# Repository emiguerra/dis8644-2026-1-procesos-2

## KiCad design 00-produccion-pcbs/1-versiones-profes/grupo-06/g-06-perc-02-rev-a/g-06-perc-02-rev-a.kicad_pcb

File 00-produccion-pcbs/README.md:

# produccion-pcbs

jornada maratónica sábado 06 junio 2026

equipo docente toma todos los proyectos de kicad entregados el día anterior, de proyecto-02, y con eso edita, revisa, y envía a producción.

hay 6 grupos de trabajo con una temática en particular, cada grupo realizó 2 esquemáticos con sus respectivas placas, en varias versiones que subieron a la carpeta 00-proyecto-02.

a continuación los apuntes de las distintas revisiones hechas de estos proyectos, para prepararlos para su producción física.

en este repo creamos 3 carpetas:

- 0-versiones-estudiantes: archivos de kicad con las versiones más recientes de proyectos de estudiantes
- 1-versiones-profes: archivos de kicad con las versiones revisadas y realizadas por equipo docentes
- 2-archivos-produccion: gerbers de producción, etiquetados como revA.

## grupo-01: piezos

- benjaminalvarez21
- Anaysval
- chknngttts
- ryukivol
- nicolasvaldesgreve

### g-01-pie-01-rev-a

- cambiamos tamaño r15
- cambiamos conector de entrada
- cambiamos nomenclatura de "100 u" a "100u"
- cambiamos huella de transistor Q1, porque era la equivocada

### g-01-pie-02-rev-a

- no fue enviado a producción porque no tenemos garantía de que funcionara según lo visto en protoboard.

## grupo-02: secuenciadores

- isidoraalvarez
- tomascatri
- dayanapanitrur
- Estrabismx
- angel-udp

### g-02-sec-01-rev-a

en esquemático:

- agregamos resistor de clock in a ground, para pulldown.
- agregamos resistor entre 4040 Q0 patita 9 y salida
- agregamos resistor a cada salida de jack switch.
- cambiamos huellas de transistores a versión inline_wide para que tengan más espacio
- agregados mounting hole faltantes

en pcb:

- actualizamos conectores jack a la huella de la biblioteca, para poder rutear bien los nuevos resistores y no perdernos.

### g-02-sec-02-rev-a

en esquemático:

- agregamos también resistores de protección en entradas y salidas.
- agregados mounting hole faltantes

en pcb:

- actualizamos conectores jack a la huella de la biblioteca, para poder rutear bien los nuevos resistores y no perdernos.

## grupo-03: osciladores 1

- vanessagarciaM
- antoloch
- ccarlabelenn
- arielorozco024
- Narelyriquelme

### g-03-osc-01-rev-a

- C1 estaba rotado, fue corregido.
- audio jack de entrada y salida estaban mal conectados
- condensador de salida fue cambiado por uno no polarizado
- renombrar C3 a 4u7
- cambiado C1 por condensador polarizado
- 40106 fue usado como dos chips distintos, en vez de usar varios schmitt triggers desde un mismo chip, tuvimos que hacer esos cambios
- volvimos a rutear casi todo, ya que se bajó de 2 chips a 1
-

### g-03-osc-02-rev-a

## grupo-04: osciladores 2

- antokiaraa
- santiagocifuvelez
- paulafuentesm
- kristelagj
- catalinaoyanedel
- yairaruiz

## grupo-05: filtros

- antoniaamc
- Catabalboa
- sebastianguevaralarotta
- CatalinaJeria
- Luisaatoro9

### g-05-fil-01-rev-a

- error grave en la nomenclatura de los proyectos: el 01 en su README dicen que es el activo, pero en Kicad es el pasivo
- cambiamos C1 por condensador no polarizado
- conectamos patita del medio de potenciómetro
- confusión en los tamaños de los condensadores C4 y C5
- los tamaños de las pistas usados no fueron los indicados en clases ni en estandarización
- faltó el paso de agregar tierra a la placa, no está hecho

### g-05-fil-02-rev-a

- error grave en la nomenclatura de los proyectos: el 01 en su README dicen que es el activo, pero en Kicad es el pasivo
- no fue enviado a producción, ya que no funcionó en protoboard

## grupo-06: percusiones

- terroiblea
- martinaechavarria-stack
- Nicolas-Miranda1312
- paredesvania
- Coff4

### g-06-perc-01-rev-a

- agregamos jack de entrada de audio que reemplace la oscilación de entrada
- agregamos ground a los integrados que no están siendo usados

### g-06-perc-02-rev-a

- agregamos el detalle de las entradas de las compuertas lógicas no usadas, fueron conectadas a tierra, para definir sus estados
- C7 estaba en el esquemático pero no en la placa, tuvimos que agregarlo
- C4 le faltaba una conexión en la PCB, la agregamos

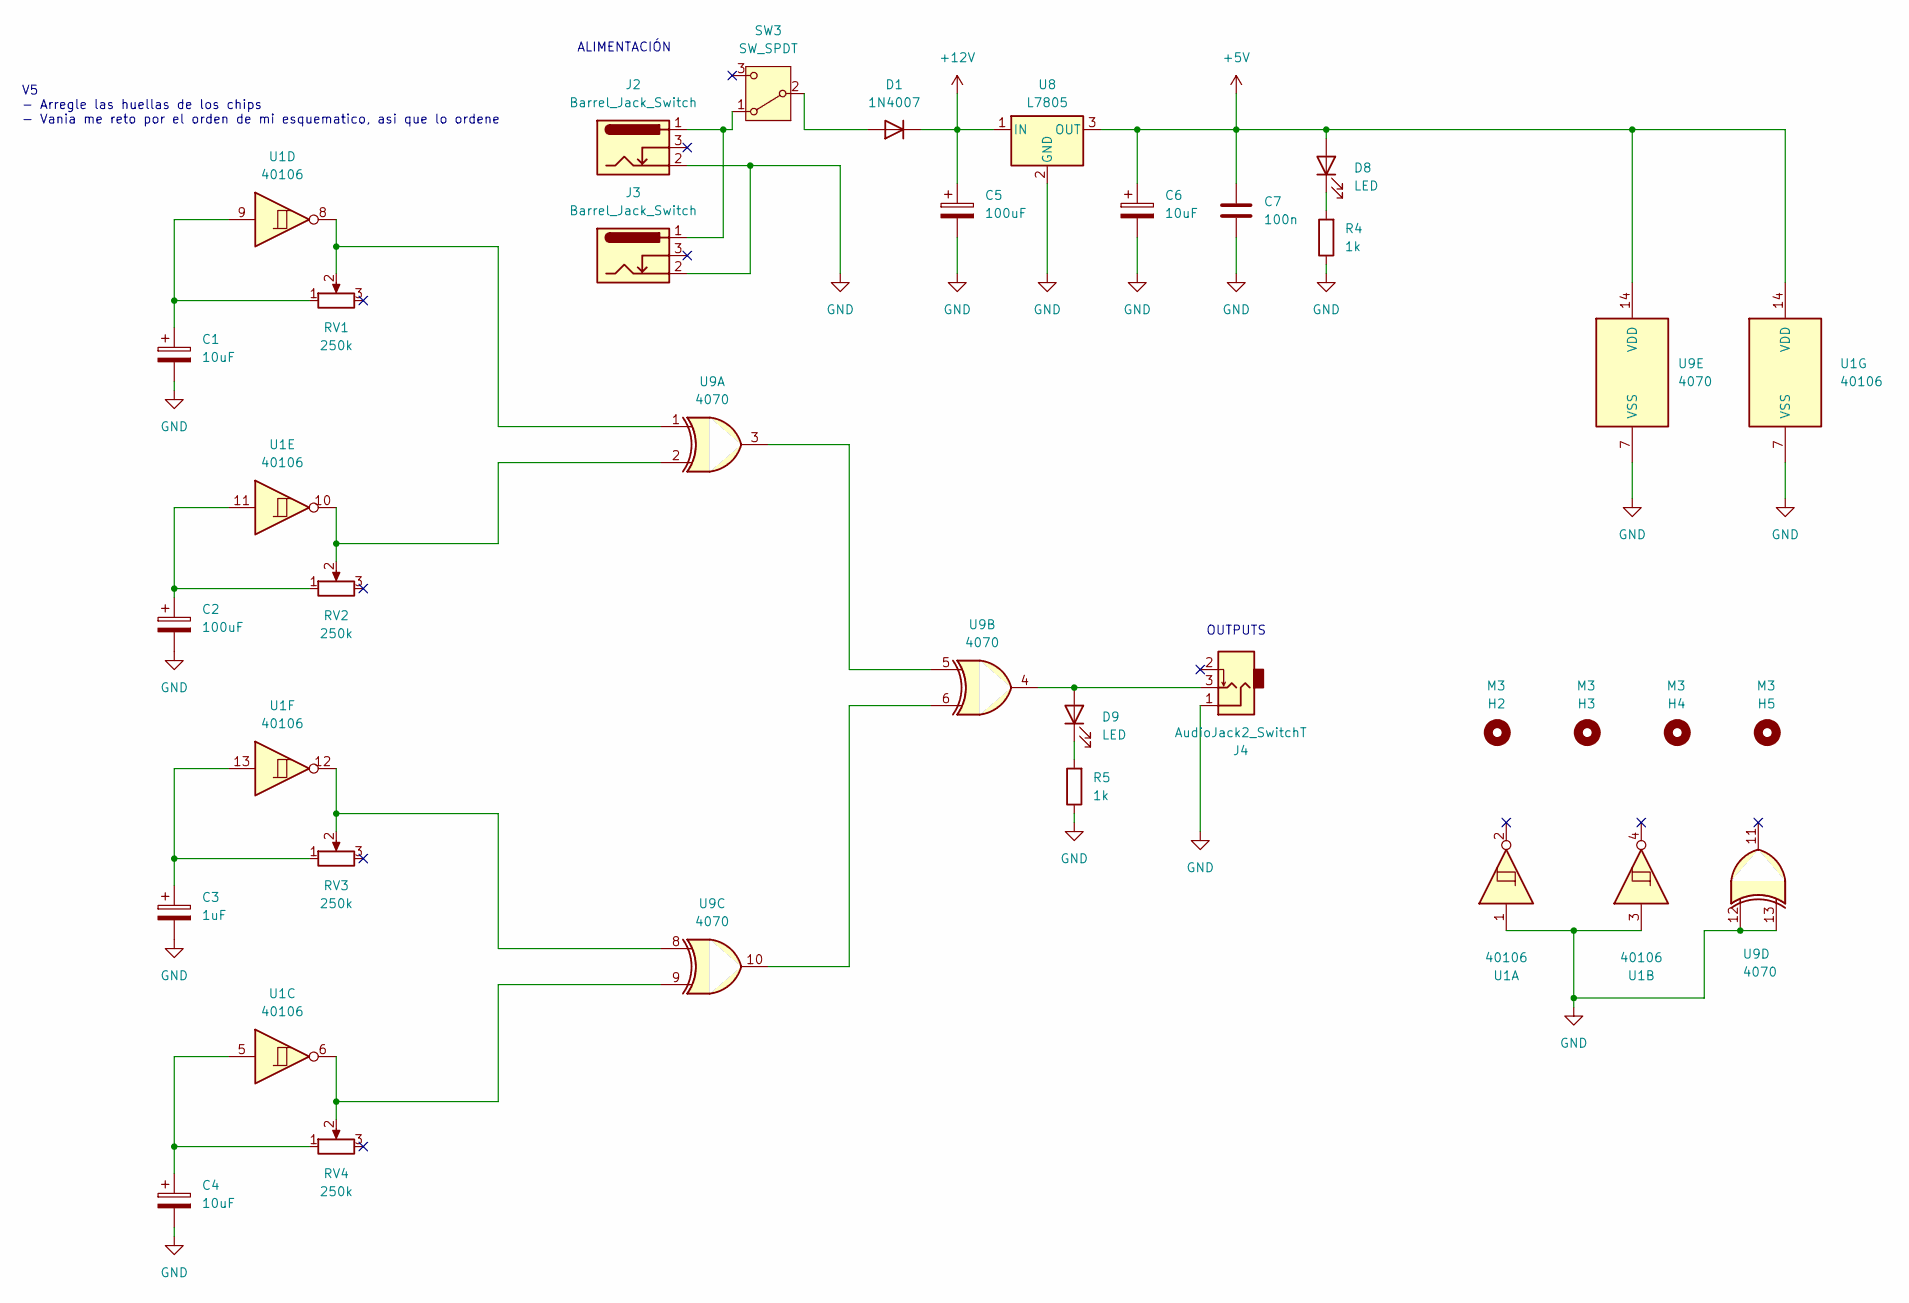
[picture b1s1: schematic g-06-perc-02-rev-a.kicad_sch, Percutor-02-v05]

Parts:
C1, C4: 10uF; CP_Radial_D8.0mm_P3.80mm
C2, C5: 100uF; CP_Radial_D8.0mm_P3.80mm
C3: 1uF; CP_Radial_D8.0mm_P3.80mm
C6: 10uF; CP_Radial_D4.0mm_P2.00mm
C7: 100n; C_Disc_D5.0mm_W2.5mm_P2.50mm
D1: 1N4007; D_DO-41_SOD81_P10.16mm_Horizontal
D8, D9: LED; LED_D5.0mm
H2, H3, H4, H5: M3; MountingHole_3.2mm_M3
J2, J3: Barrel_Jack_Switch; BarrelJack_Horizontal
J4: AudioJack2_SwitchT; PJ301M-12
R4, R5: 1k; R_Axial_DIN0207_L6.3mm_D2.5mm_P10.16mm_Horizontal
RV1, RV2, RV3, RV4: 250k; Potentiometer_Alps_RK163_Single_Horizontal
SW3: SW_SPDT; spdt_ssd12d00g3
U1: 40106; DIP-14_W7.62mm_LongPads
U8: L7805; TO-220-3_Horizontal_TabDown
U9: 4070; DIP-14_W7.62mm_LongPads

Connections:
+5V: C6.1, C7.1, D8.2 (A), U1.14 (VDD), U8.3 (OUT), U9.14 (VDD)
+12V: C5.1, D1.1 (K), U8.1 (IN)
GND: C1.2, C2.2, C3.2, C4.2, C5.2, C6.2, C7.2, J2.2, J3.2, J4.1, R4.1, R5.1, U1.1, U1.3, U1.7 (VSS), U8.2 (GND), U9.7 (VSS), U9.12, U9.13
unnamed: C1.1, RV1.1, U1.9
unnamed: C2.1, RV2.1, U1.11
unnamed: C3.1, RV3.1, U1.13
unnamed: C4.1, RV4.1, U1.5
unnamed: D1.2 (A), SW3.2 (B)
unnamed: D8.1 (K), R4.2
unnamed: D9.2 (A), J4.3, U9.4
unnamed: D9.1 (K), R5.2
unnamed: RV1.2, U1.8, U9.1
unnamed: RV2.2, U1.10, U9.2
unnamed: RV3.2, U1.12, U9.8
unnamed: RV4.2, U1.6, U9.9
unnamed: J2.1, J3.1, SW3.1 (A)
unnamed: U9.3, U9.5
unnamed: U9.6, U9.10

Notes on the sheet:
ALIMENTACIÓN
OUTPUTS
V5 - Arregle las huellas de los chips - Vania me reto por el orden de mi esquematico, asi que lo ordene

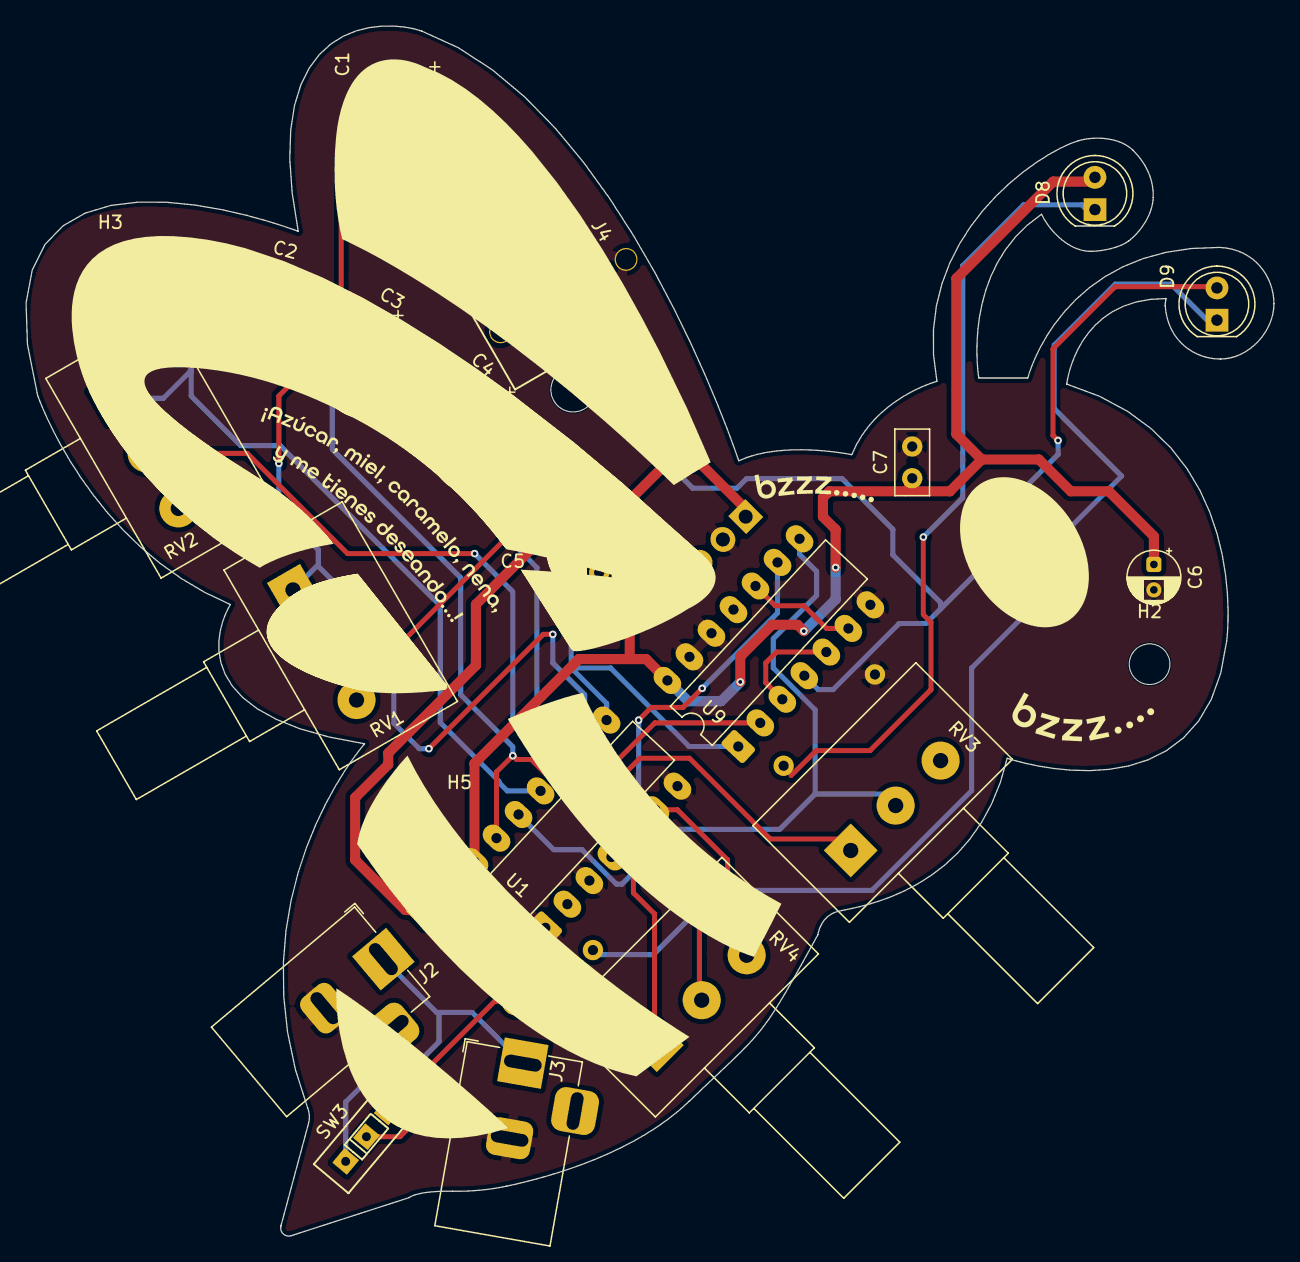
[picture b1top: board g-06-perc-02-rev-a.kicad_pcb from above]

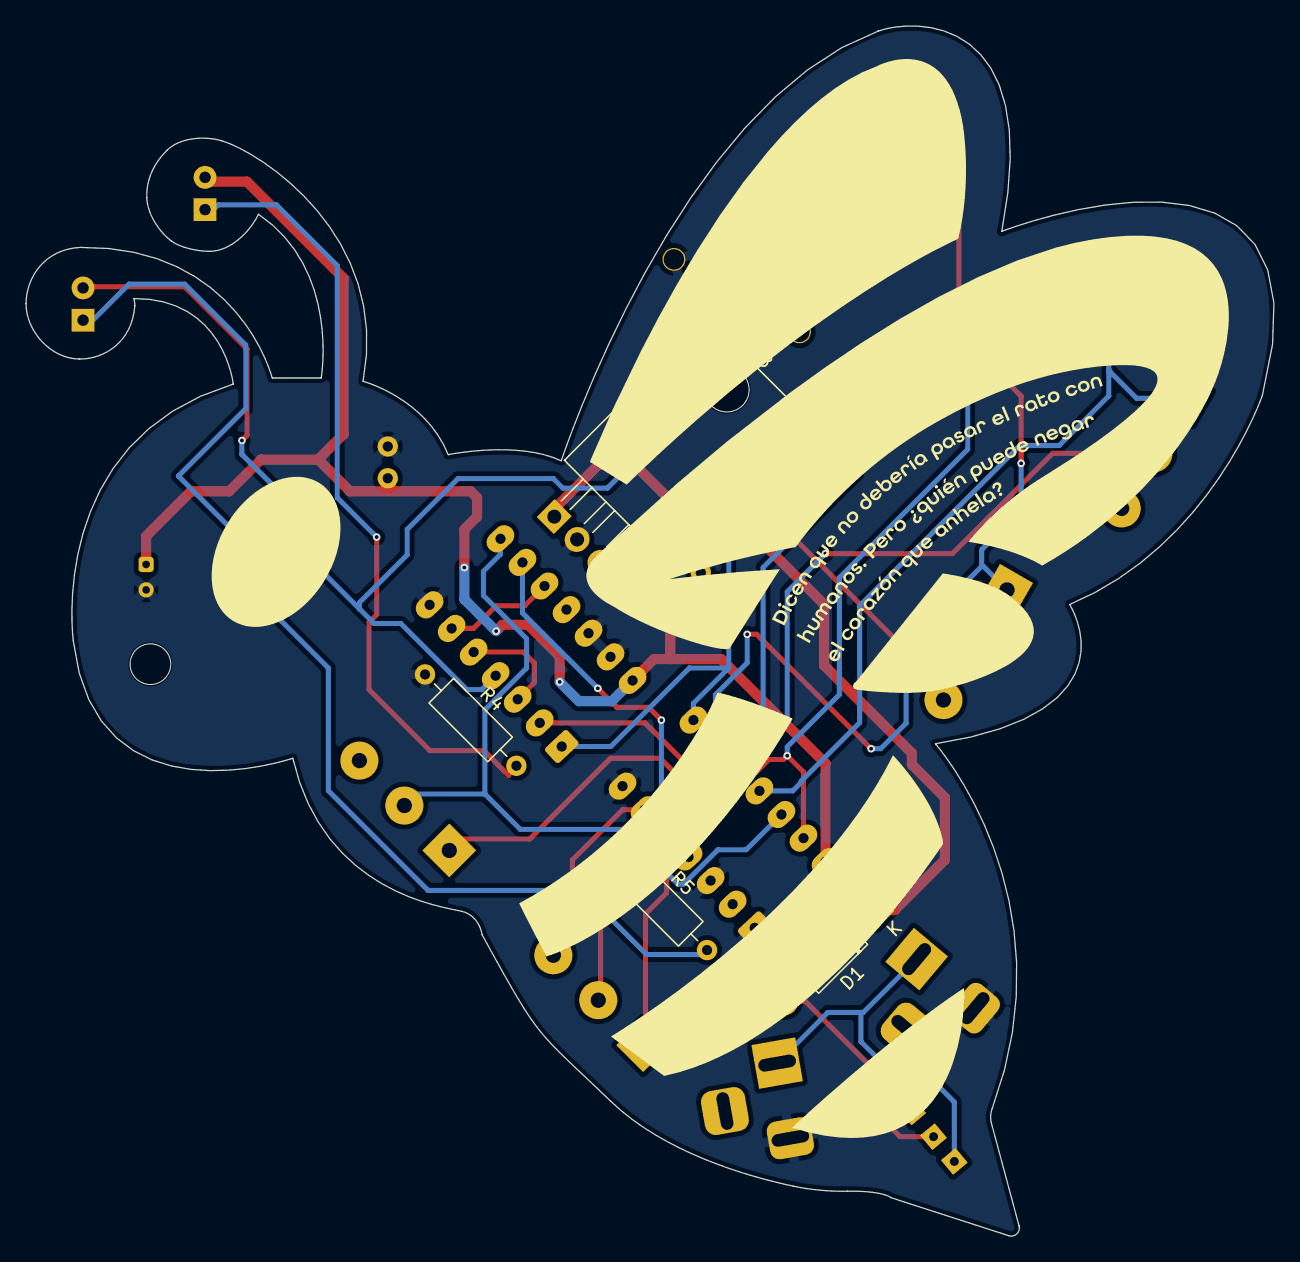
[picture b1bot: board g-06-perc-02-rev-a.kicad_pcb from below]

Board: 2 copper layers, 98.2 x 95.2 mm, 27 parts (4 on the bottom side), 18 nets.

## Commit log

2026-05-15 me-faltó-una
2026-05-19 Add date to README for sesion-10b
2026-05-19 porfavor-cambia-el-tamano-juro-que-son-de-400px
2026-05-19 apuntes
    Updated section headers and added new content about OSC and chips.
2026-05-22 sesion-in-correcta
2026-05-25 Feriado no hubo clases.md
2026-05-25 misaaapuntes
2026-05-25 Expand README with oscillator and 4046 chip details
    Added detailed explanation of the oscillator and the 4046 chip, including its functions and applications.
2026-05-26 ajuste
2026-05-29 agrego ceina
2026-06-02 agrego un poco libro
2026-06-02 avance 11a
2026-06-03 cambiar-carpeta
2026-06-03 Rename piezo-02-v03_pcb.kicad_pcb to piezo-02-v03.kicad_pcb
2026-06-03 agregar kicanvas
2026-06-03 arreglo bom
2026-06-05 Create ssss
2026-06-06 corregir subtitulos
2026-06-06 agregar mas texto explicativo sobre repo
2026-06-06 añadido g06-02
2026-06-06 agregar mas apuntes
2026-06-08 Update README with session details and project issues
    Added details about the class session and project presentation challenges.
2026-06-17 agrego bom maincra
2026-06-18 Update README with insights on Yoko Ono's work
    Added reflections on Yoko Ono's book and personal experiences.
